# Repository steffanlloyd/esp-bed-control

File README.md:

# esp-bed-control

This project defines a voice-control module designed to allow voice control of hospital beds for. This allows patients who are unable to use the pendant normally attached to the bed to adjust their bed position themselves.

The device is based on the ESP BOX by espressif. This is a self-contained unit that includes an ESP32-S3, speakers, a microphone, and a screen. It also includes software for voice control.

The device itself is designed to be modular for use on a wide variety of beds. It consists of 3 major components:
  - The ESP Box (performs the voice recognition, user feedback, and logic).
  - The ESP hospital bed dock. This is a custom PCB that the ESP box can dock onto. It takes signals from 6 GPIO pins and routes them to 6 solid-state relays. These relays act as "loop closures", simulating a real hospital bed pendant. These 6 loop closures have 12 associated leads that are mapped to the first 12 pins of a male DB25 port. The dock also has a USB-C port for charging, and an RJ45 port that was only included to allow for future expansion of the project, but is not currently in use.
  - The hospital bed interface PCB. This is another custom PCB which must be designed specifically for the bed in question. Its role is to take the loop closers from the DB25 port on the dock PCB, and map them to the right pins of the pendant. It should connect to the bed, and to the pendant, such that the pendant continues to work as normal. We have designed one such interface board for the "New Span America" hospital beds. 

The hookup diagram is shown below.

The entire device is housed inside a 3D printed shell. The STL files for this shell are included in the /cad folder.

Documentation can be found in ``docs/instructions.pdf``.

## Available Commands

When you plug in the ESP box (after its been flashed and assembled), it will startup for a short period then "ding" to indicate that it is ready. It can then be woken with the wake word "Hi E.S.P.". Once it has woken, any of the following commands may be issued:
- Headrest up/down
- Legrest up/down
- Bed up/down
Each of these commands can be modified with "a little bit", "way", or "fully", e.g. "Headrest a little up", "Headrest way up", or "Headrest fully up". The nominal command closes the relay for 2 seconds. "A little bit" is only 1 second, "way" is 4 seconds, and "fully" is 15 seconds.

## PCB Manufacturing

To manufacture the PCB, you will need to have some experience with custom PCB manufacturing. Kicad schematics and PCB layouts are provided for all boards, as well as PDF's. These are all in the /pcb folder.

## Programming the ESP Box

Programming the ESP box is a bit challenging, since documentation is limited. However, our program is relatively well commented and is included here under the /src folder. The main components of this software are listed below:
  - ``main.c``: Initiates the program, assigns the GPIO pins
  - ``/gui/ui_sr.c``: Includes the code to how the UI displays for the speech recognition.
  - ``/gui/ui_main.c``: Includes other code on how the UI works
  - ``/app/app_audio.c``: Initializes the speaker output.
  - ``/app/app_lvgl.c``: Initializes the screen of the devices.
  - ``/app/app_sr_handler.c``: Contains the logic of how to respond to different voice commands.
  - ``/app/app_sr.c``: Contains code for the actual voice recognition itself.

## Flashing the ESP Box

To flash the ESP box, follow these steps.
1. Open/Install VScode, and install the Espressif IDE plugin. [Instructions here](https://docs.espressif.com/projects/esp-idf/en/latest/esp32/get-started/index.html). You may take some time to get familiar with the programming environment.
2. Next, setting up development environment. Please refer to [ESP-IDF (release/v5.0)](https://docs.espressif.com/projects/esp-idf/en/release-v4.4/esp32s3/get-started/index.html#installation-step-by-step) Installation Step by Step.
3. Run command ``git clone --recursive https://github.com/espressif/esp-box.git`` somewhere on your machine to download the code of this project and then switch the ESP-IDF version to specified version.
4. Open up the ``/src`` folder and link the "components" of the project in ``CMakeLists.txt``. E.g., replace the lines
  ```
  set(EXTRA_COMPONENT_DIRS
      path/to/esp-box/components
      )
  ```
5. Connect, build and flash the device.

## Customizing the voice commands

In VS code, open the ESP-IDF Terminal (it may already be open, otherwise there is a button in the bottom that opens it). To customize the voice commands you need to run the ``idf.py menuconfig`` command, and customize the commands that the board listens to.  This is done under the ``ESP Speech Recognition`` menu item, followed by ``Add English speech commands``. You may also customize the wakeword under the ``Select wake words`` menu item.

You will need to generate the G2P phrase for each voice command. A description of how to do this is given in ``esp-box/components/esp-sr/tool``. A list of the G2P commands for all the default commands are given in ``docs/commands.xlsx``.

Once this is complete, you should modify the handling of each of these voice commands with appropriate modifications to ``app/app_sr_handler.c``. Each voice command in the menuconfig settings is keyed to its ID number, so the ``app_sr_handler`` code simply runs that ID through a switch statement to run the appropriate code.

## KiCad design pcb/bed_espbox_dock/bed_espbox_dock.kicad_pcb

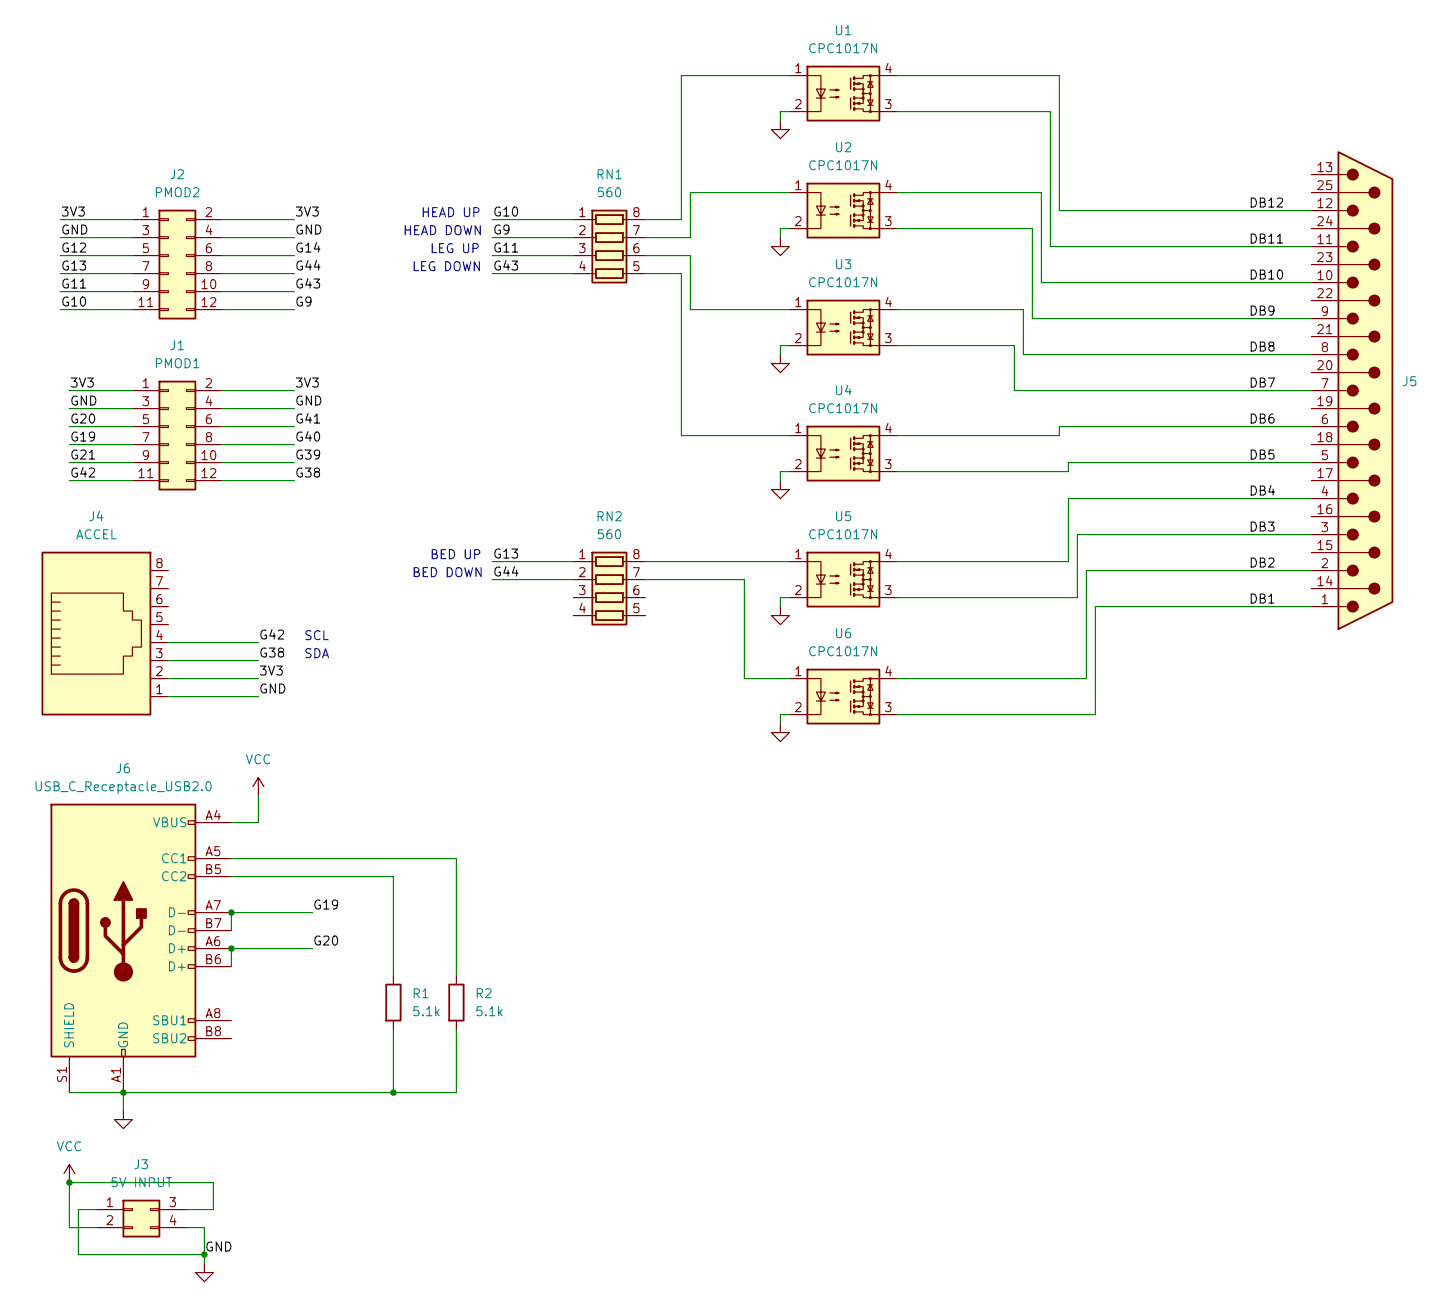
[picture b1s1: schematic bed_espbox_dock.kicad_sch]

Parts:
J1: PMOD1; PinHeader_2x06_P2.54mm_Vertical
J2: PMOD2; PinHeader_2x06_P2.54mm_Vertical
J3: 5V INPUT; PinHeader_2x02_P2.54mm_Vertical
J4: ACCEL; RJ45_Amphenol_54602-x08_Horizontal
J5: DB25_Male; DSUB-25_Male_Horizontal_P2.77x2.84mm_EdgePinOffset7.70mm_Ho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
J6: USB_C_Receptacle_USB2.0; USB_C_Receptacle_GCT_USB4105-xx-A_16P_TopMnt_Horizontal
R1, R2: 5.1k; R_0603_1608Metric
RN1, RN2: 560; R_Array_Convex_4x0603
U1, U2, U3, U4, U5, U6: CPC1017N; SOP-4_3.8x4.1mm_P2.54mm

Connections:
/3V3: J1.1, J1.2, J2.1, J2.2, J4.2
/DB1: J5.1, U6.3
/DB2: J5.2, U6.4
/DB3: J5.3, U5.3
/DB4: J5.4, U5.4
/DB5: J5.5, U4.3
/DB6: J5.6, U4.4
/DB7: J5.7, U3.3
/DB8: J5.8, U3.4
/DB9: J5.9, U2.3
/DB10: J5.10, U2.4
/DB11: J5.11, U1.3
/DB12: J5.12, U1.4
/G9: J2.12, RN1.2 (R2.1)
/G10: J2.11, RN1.1 (R1.1)
/G11: J2.9, RN1.3 (R3.1)
/G12: J2.5
/G13: J2.7, RN2.1 (R1.1)
/G14: J2.6
/G19: J1.7, J6.A7 (D-), J6.B7 (D-)
/G20: J1.5, J6.A6 (D+), J6.B6 (D+)
/G21: J1.9
/G38: J1.12, J4.3
/G39: J1.10
/G40: J1.8
/G41: J1.6
/G42: J1.11, J4.4
/G43: J2.10, RN1.4 (R4.1)
/G44: J2.8, RN2.2 (R2.1)
GND: J1.3, J1.4, J2.3, J2.4, J3.1, J3.4, J4.1, J6.A1 (GND), J6.A12 (GND), J6.B1 (GND), J6.B12 (GND), J6.S1 (SHIELD), R1.2, R2.2, U1.2, U2.2, U3.2, U4.2, U5.2, U6.2
unnamed: J6.A5 (CC1), R2.1
unnamed: J6.B5 (CC2), R1.1
unnamed: RN1.5 (R4.2), U4.1
unnamed: RN1.6 (R3.2), U3.1
unnamed: RN1.7 (R2.2), U2.1
unnamed: RN1.8 (R1.2), U1.1
unnamed: RN2.7 (R2.2), U6.1
unnamed: RN2.8 (R1.2), U5.1
VCC: J3.2, J3.3, J6.A4 (VBUS), J6.A9 (VBUS), J6.B4 (VBUS), J6.B9 (VBUS)

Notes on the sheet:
BED DOWN
SCL
SDA
LEG DOWN
BED UP
LEG UP
HEAD DOWN
HEAD UP

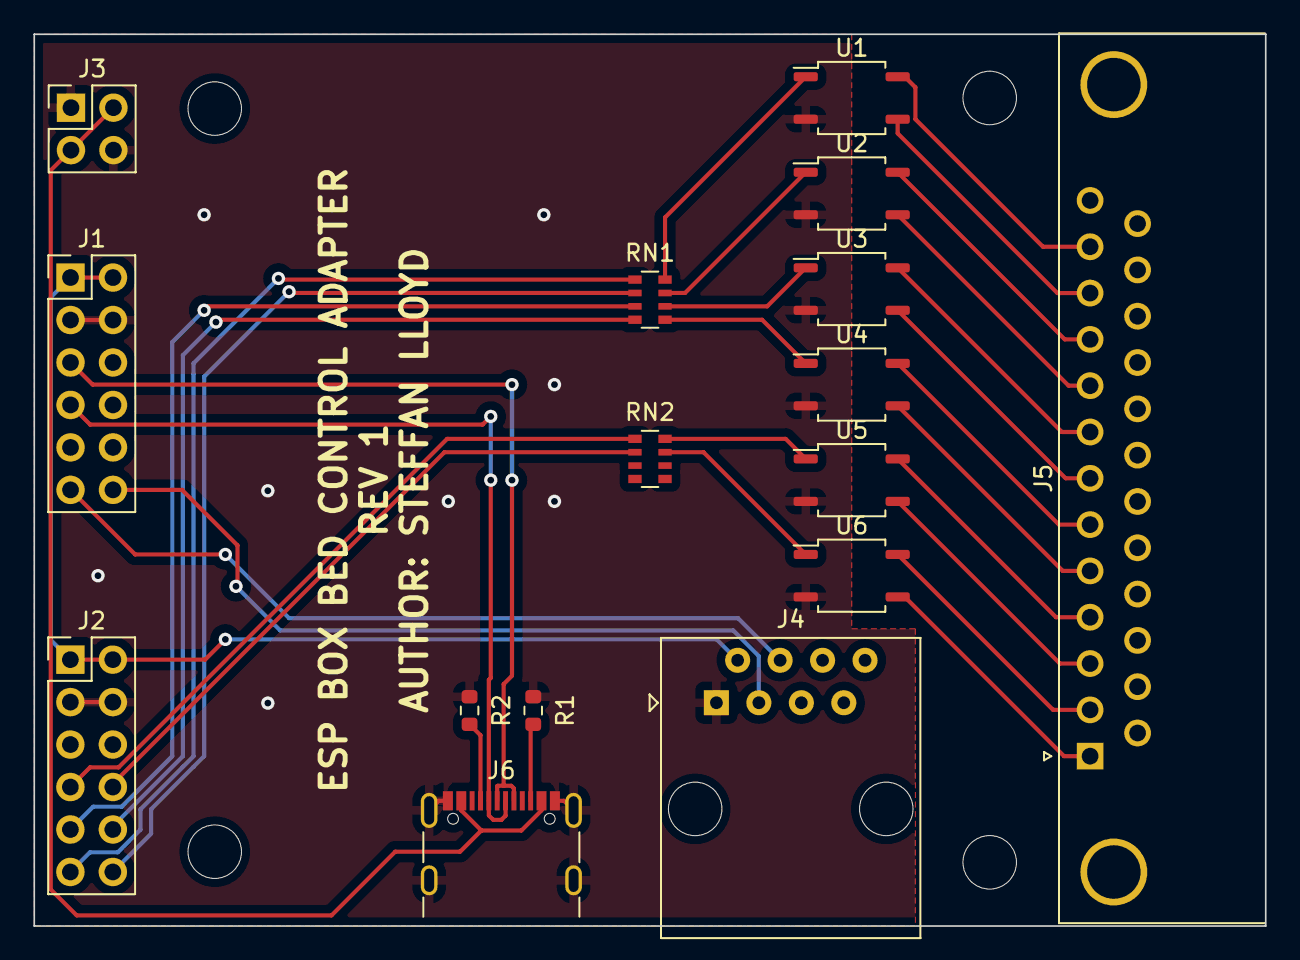
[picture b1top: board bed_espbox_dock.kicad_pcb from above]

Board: 2 copper layers, 73.7 x 53.3 mm, 16 parts (0 on the bottom side), 33 nets.

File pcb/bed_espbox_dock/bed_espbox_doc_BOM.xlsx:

BOM
Name | Qty | ID | Digikey Part ID | Component ID
SS Relay | 6 | CPC1017NTR | CLA233CT-ND | U1,U2,U3,U4,U5,U6
RJ45 Jack | 1 | 54602-908LF | 609-1046-ND | J4
USB C | 1 | USB4085-GF-A | 2073-USB4105-GF-ACT-ND | J6
DB25 Male | 1 | A-DS 25 A/KG-T2S | AE10980-ND | J5
Resistor array | 2 | CAY16-561J4LF | CAY16-561J4LFCT-ND | RN1,RN2
Grounding resistor | 2 | ERJ-2GEJ512X | P5.1KJCT-ND | R1,R2
Male header 12 | 2 | PH2-12-UA | 2057-PH2-12-UA-ND | J1,J2
Male header 4 | 1 | PH2-04-UA | 2057-PH2-04-UA-ND | J3

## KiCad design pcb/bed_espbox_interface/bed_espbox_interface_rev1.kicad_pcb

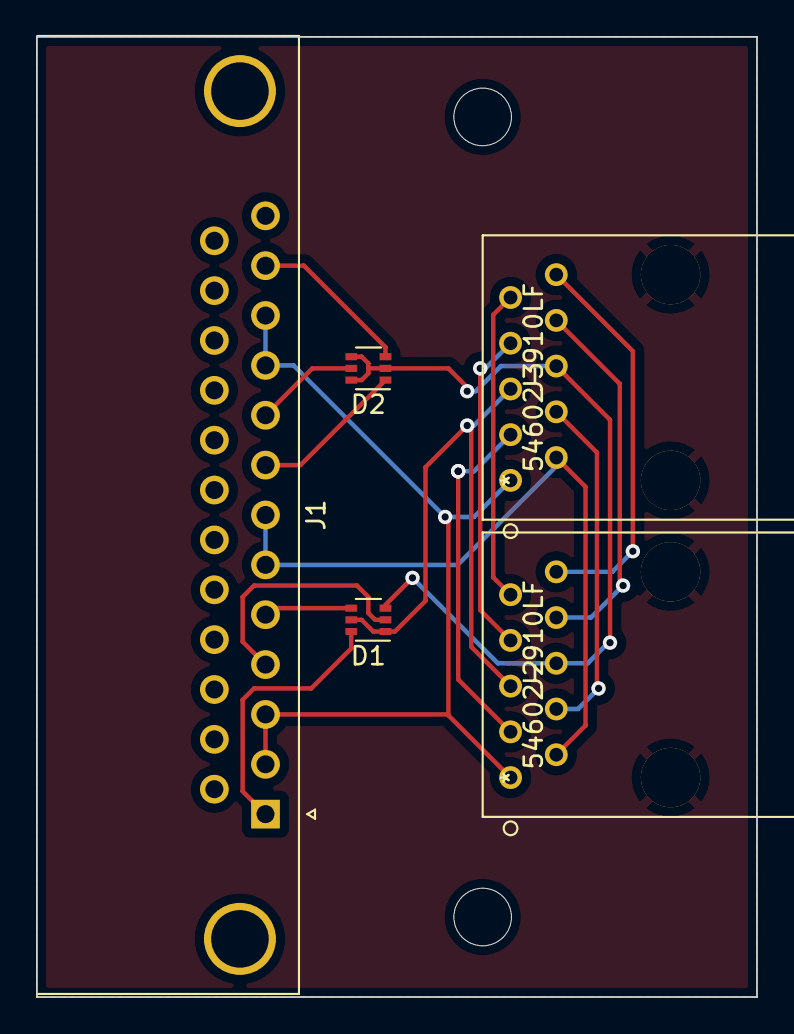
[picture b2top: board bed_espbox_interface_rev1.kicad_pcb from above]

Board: 2 copper layers, 40.0 x 53.3 mm, 5 parts (0 on the bottom side), 17 nets.

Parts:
D1, D2: MMBD4448HTW; SOT-363_SC-70-6
J1: DB25_Male; DSUB-25_Female_Horizontal_P2.77x2.84mm_EdgePinOffset9.90mm_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
J2, J3: 54602-910LF

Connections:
/P1: J1.2, J1.3, J1.10, J1.11, J2.1, J3.1
/P2: J1.6, J1.7, J2.2, J3.2
/P3: J2.3, J3.3
/P4: J2.4, J3.4
/P5: D1.1 (A), D1.5 (K), J2.5, J3.5
/P6: D1.3 (A), D2.2 (A), D2.4 (K), D2.6 (K), J2.6, J3.6
/P7: J2.7, J3.7
/P8: J2.8, J3.8
/P9: J2.9, J3.9
/P10: J2.10, J3.10
GND: J2.11, J2.12, J3.11, J3.12
unnamed: D1.6 (K), J1.1
unnamed: D1.2 (A), J1.4
unnamed: D1.4 (K), J1.5
unnamed: D2.1 (A), J1.8
unnamed: D2.5 (K), J1.9
unnamed: D2.3 (A), J1.12

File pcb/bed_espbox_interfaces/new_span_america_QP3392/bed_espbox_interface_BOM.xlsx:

BOM
Name | Qty | ID | Digikey Part ID | Component ID
DB25 Female | 1 | A-DF 25 A/KG-T4S | AE10937-ND | J1
RJ50 Jack | 2 | 54602-910LF | 609-1047-ND | J2,J3
Diode 2x | 2 | MMBD4448HTM-7-F | MMBD4448HTM-FDICT-ND | D1,D2

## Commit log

2023-01-22 Added codebase and docs
2023-01-22 Added cad and electrical files
2023-01-23 Updated readme and reorganized
2023-01-25 Updates to config and README
2023-01-25 UPdate to readme
2023-01-25 Housekeeping

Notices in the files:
parts and their libraries:
Copyright 2021 Accelerated Designs. All rights reserved.
